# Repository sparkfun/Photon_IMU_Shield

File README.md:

SparkFun Photon IMU Shield
========================================

[*SparkFun Photon IMU Shield (DEV-13629)*](https://www.sparkfun.com/products/13629)

The [SparkFun Photon IMU Shield](https://www.sparkfun.com/products/13629) is a versatile motion-sensing add-on board for your Photon. It features an LSM9DS1 system-in-a-chip that houses a 3-axis accelerometer, 3-axis gyroscope, and 3-axis magnetometer. That’s right, 9 degrees of freedom (9DOF) from a single IC!

Each sensor in the LSM9DS1 supports a large variety of ranges: the accelerometer’s scale can be set to ± 2, 4, 6, 8, or 16 g, the gyroscope supports ± 245, 500, and 2000 °/s, and the magnetometer has full-scale ranges of ± 2, 4, 8, or 12 gauss. The SparkFun Photon IMU Shield comes with the headers already soldered on, so you can plug and play!

Repository Contents
-------------------

* **/Hardware** - Eagle design files (.brd, .sch)
* **/Production** - Production panel files (.brd)
* **/Libraries** - Firmware library and example code for the Particle Photon.

Documentation
--------------
* **[Hookup Guide](https://learn.sparkfun.com/tutorials/photon-imu-shield-hookup-guide)** - Hardware overview and example code.

Product Versions
----------------
* [DEV-13629](https://www.sparkfun.com/products/13629)- V1.0 release of the Photon IMU Shield.

License Information
-------------------
This product is _**open source**_! 

The **hardware** is released under [Creative Commons ShareAlike 4.0 International](https://creativecommons.org/licenses/by-sa/4.0/).

The **code**  license can be found in the source directory.

Please use, reuse, and modify these files as you see fit. Please maintain attribution to SparkFun Electronics and release anything derivative under the same license.

Distributed as-is; no warranty is given.

- Your friends at SparkFun.

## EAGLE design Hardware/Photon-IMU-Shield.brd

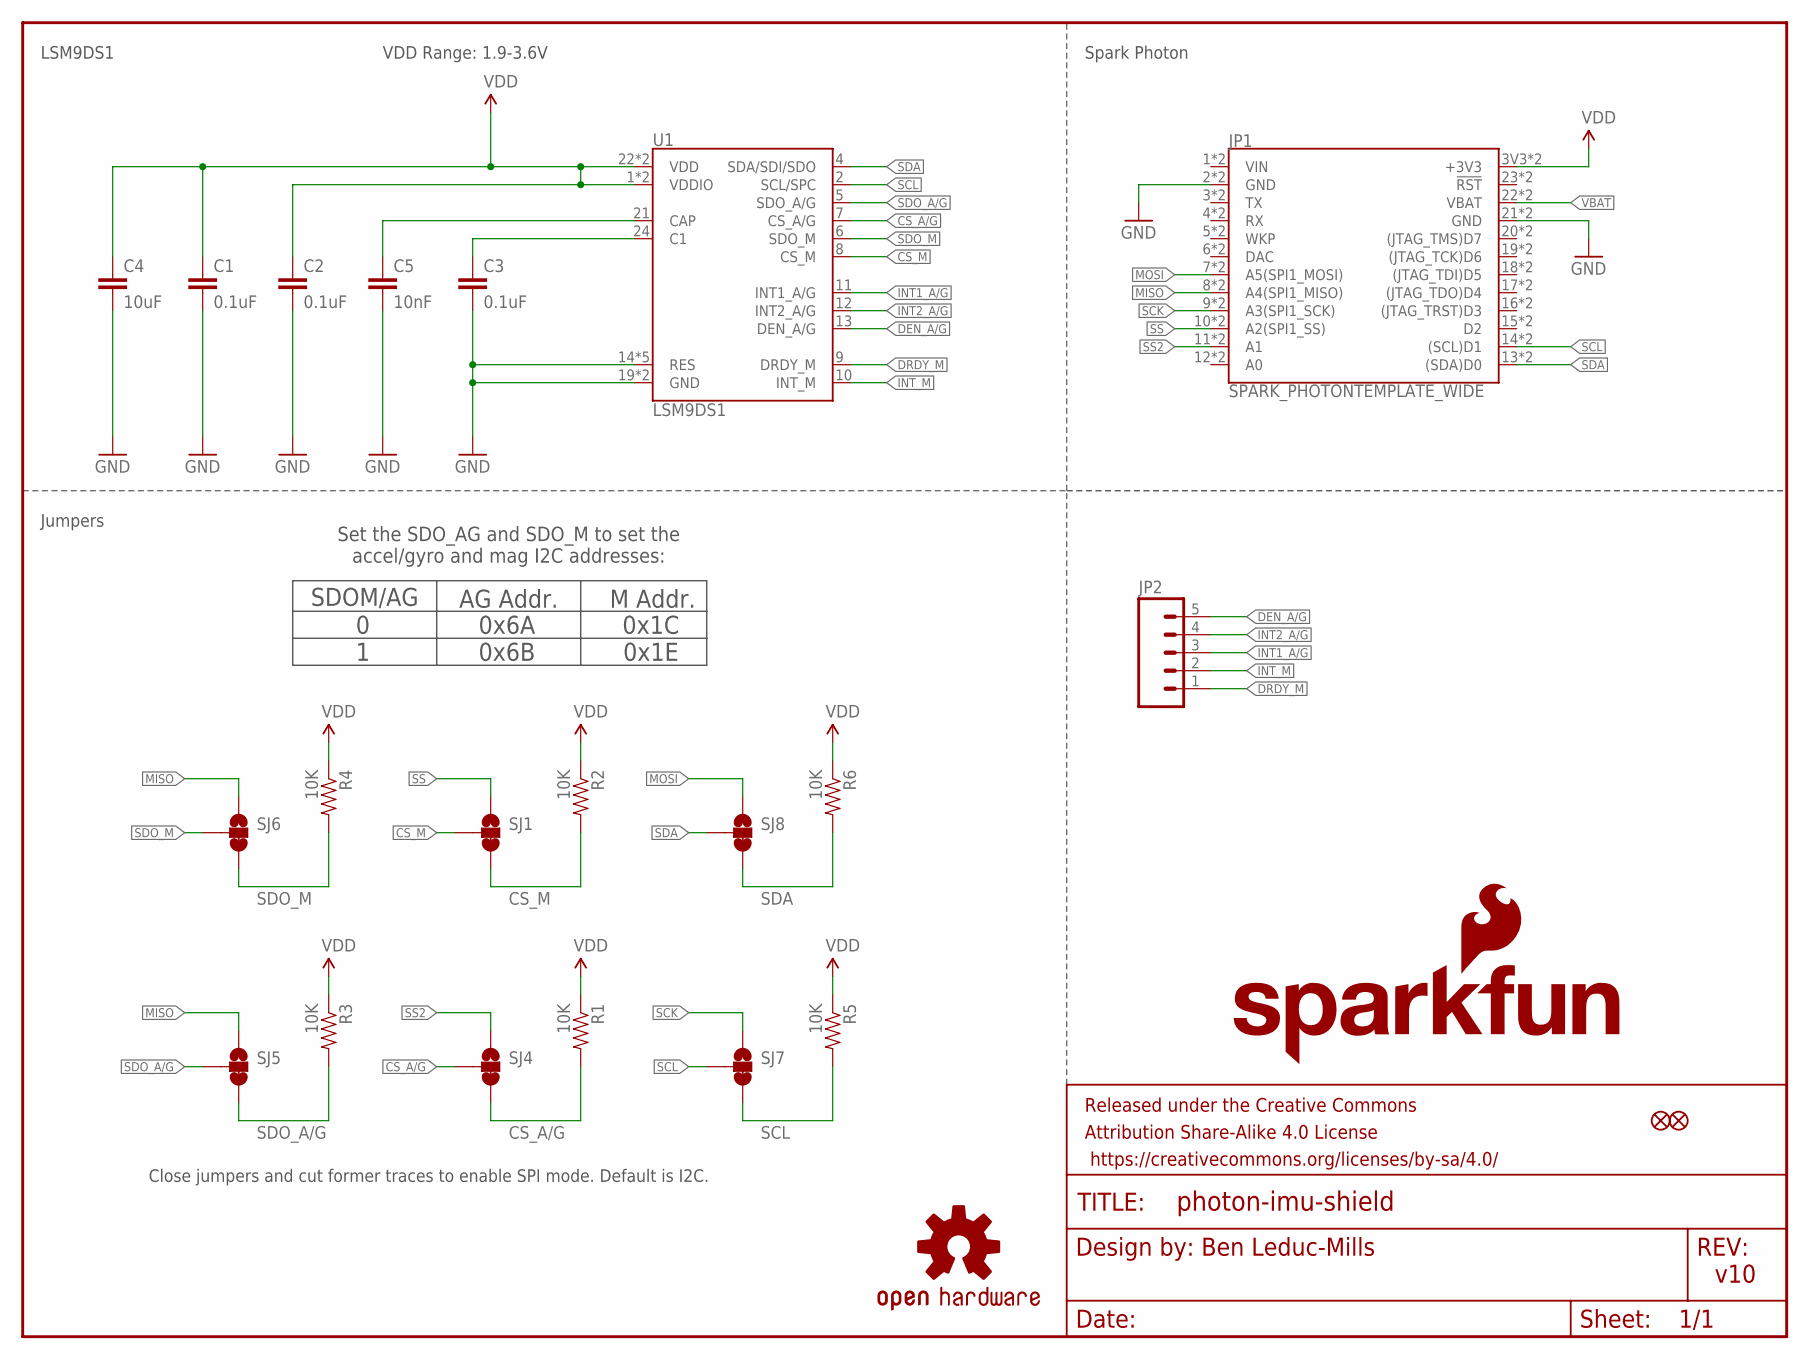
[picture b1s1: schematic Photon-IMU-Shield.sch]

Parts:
C1, C2, C3: 0.1uF; 0603-CAP
C4: 10uF; 0603-CAP
C5: 10nF; 0603-CAP
FID1, FID2: FIDUCIAL1X2; FIDUCIAL-1X2
FRAME1: FRAME-LETTER; CREATIVE_COMMONS
JP1: SPARK_PHOTONTEMPLATE_WIDE; SPARK_PHOTON_TEMPLATE_WIDE
JP2: M05PTH; 1X05
LOGO1: SFE_LOGO_NAME_FLAME.1_INCH; SFE_LOGO_NAME_FLAME_.1
LOGO2: OSHW-LOGOS; OSHW-LOGO-S
R1, R2, R3, R4, R5, R6: 10K; 0603-RES
SJ1, SJ4, SJ5, SJ6, SJ7, SJ8: JUMPER-PAD-3-2OF3_NC_BY_TRACE_SMALL; PAD-JUMPER-3-2OF3_NC_BY_TRACE_YES_SILK_FULL_BOX
U1: LSM9DS1; LGA24-8X4

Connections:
CS_A/G: R1.2, SJ4.2, SJ4.3, U1.7 (CS_A/G)
CS_M: R2.2, SJ1.2, SJ1.3, U1.8 (CS_M)
DEN_A/G: JP2.5, U1.13 (DEN_A/G)
DRDY_M: JP2.1, U1.9 (DRDY_M)
GND: C1.2, C2.2, C3.2, C4.2, C5.2, JP1.2 (GND), JP1.21 (GND), JP1.GND@0 (GND), JP1.GND@2 (GND), U1.14 (RES), U1.15 (RES), U1.16 (RES), U1.17 (RES), U1.18 (RES), U1.19 (GND), U1.20 (GND)
INT1_A/G: JP2.3, U1.11 (INT1_A/G)
INT2_A/G: JP2.4, U1.12 (INT2_A/G)
INT_M: JP2.2, U1.10 (INT_M)
MISO: JP1.8 (A4(SPI1_MISO)), JP1.A4 (A4(SPI1_MISO)), SJ5.1, SJ6.1
MOSI: JP1.7 (A5(SPI1_MOSI)), JP1.A5 (A5(SPI1_MOSI)), SJ8.1
unnamed: C5.1, U1.21 (CAP)
unnamed: C3.1, U1.24 (C1)
SCK: JP1.9 (A3(SPI1_SCK)), JP1.A3 (A3(SPI1_SCK)), SJ7.1
SCL: JP1.14 ((SCL)D1), JP1.D1 ((SCL)D1), R5.2, SJ7.2, SJ7.3, U1.2 (SCL/SPC)
SDA: JP1.13 ((SDA)D0), JP1.D0 ((SDA)D0), R6.2, SJ8.2, SJ8.3, U1.4 (SDA/SDI/SDO)
SDO_A/G: R3.2, SJ5.2, SJ5.3, U1.5 (SDO_A/G)
SDO_M: R4.2, SJ6.2, SJ6.3, U1.6 (SDO_M)
SS: JP1.10 (A2(SPI1_SS)), JP1.A2 (A2(SPI1_SS)), SJ1.1
SS2: JP1.11 (A1), JP1.A1, SJ4.1
VBAT: JP1.22 (VBAT), JP1.VBAT
VDD: C1.1, C2.1, C4.1, JP1.3V3 (+3V3), JP1.24 (+3V3), R1.1, R2.1, R3.1, R4.1, R5.1, R6.1, U1.1 (VDDIO), U1.3 (VDDIO), U1.22 (VDD), U1.23 (VDD)

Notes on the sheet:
Close jumpers and cut former traces to enable SPI mode. Default is I2C.
VDD Range: 1.9-3.6V
LSM9DS1
Spark Photon
Jumpers
SDOM/AG
0x1C 0x1E
AG Addr.
0 1
M Addr.
0x6A 0x6B
Set the SDO_AG and SDO_M to set the accel/gyro and mag I2C addresses:
v10

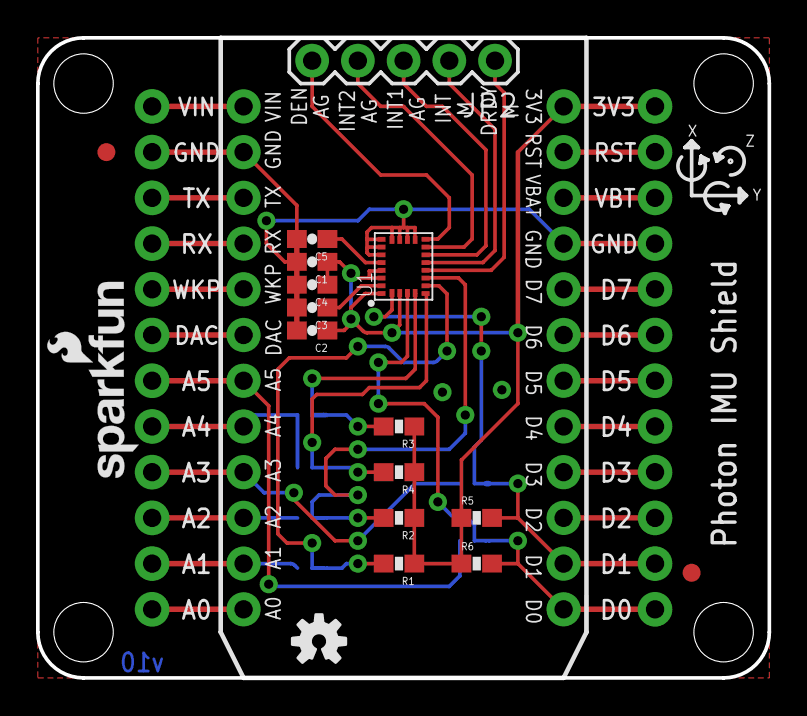
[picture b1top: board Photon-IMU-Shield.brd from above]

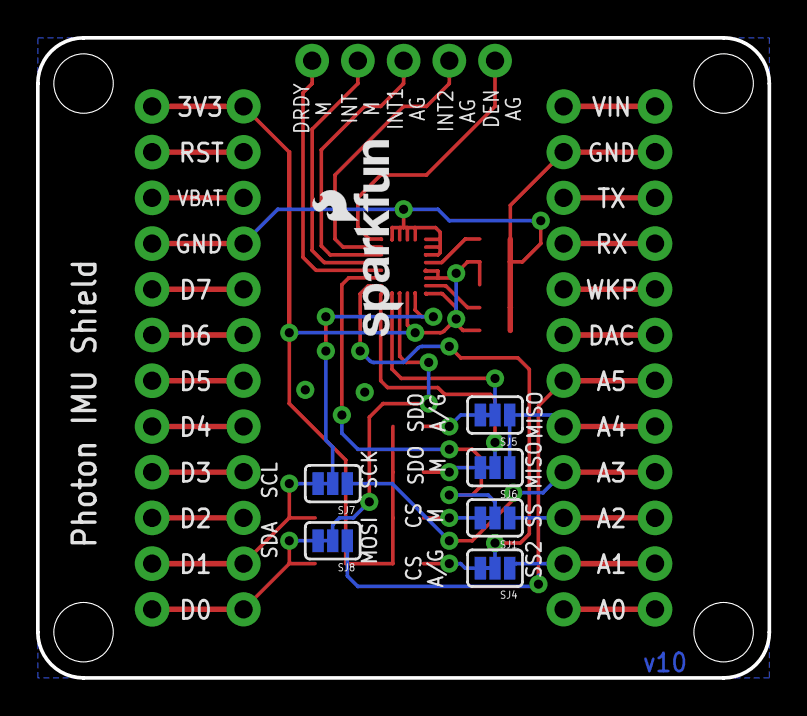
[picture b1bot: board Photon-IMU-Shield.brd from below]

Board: 2 copper layers, 40.6 x 35.6 mm, 26 parts (7 on the bottom side), 21 nets.

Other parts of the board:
U$5: SFE_LOGO_NAME_FLAME_.1

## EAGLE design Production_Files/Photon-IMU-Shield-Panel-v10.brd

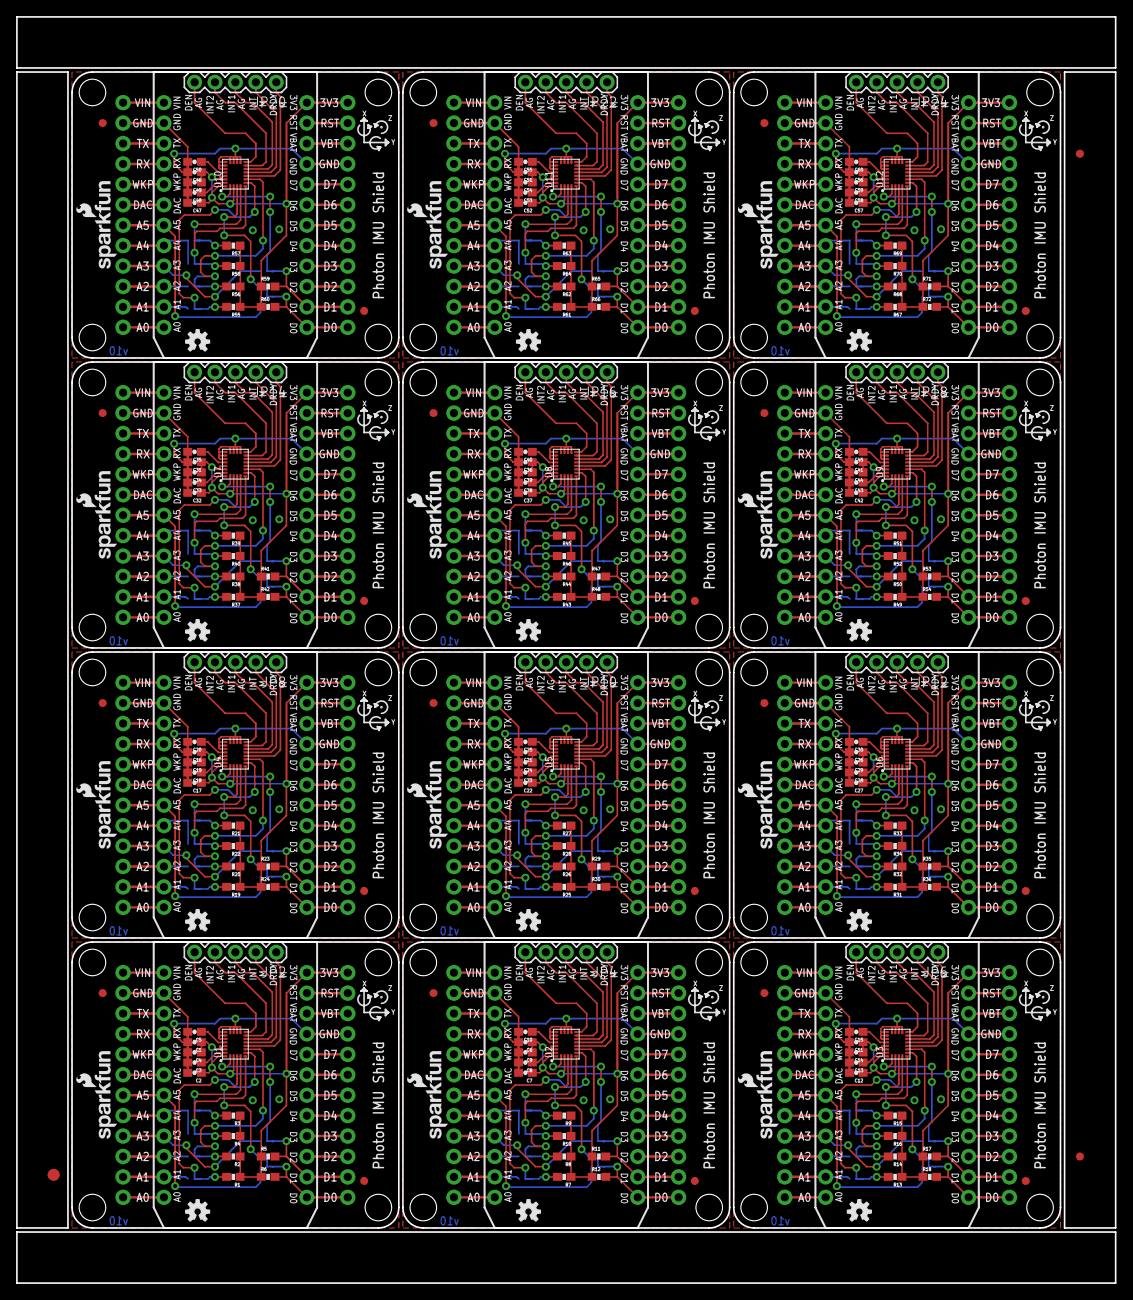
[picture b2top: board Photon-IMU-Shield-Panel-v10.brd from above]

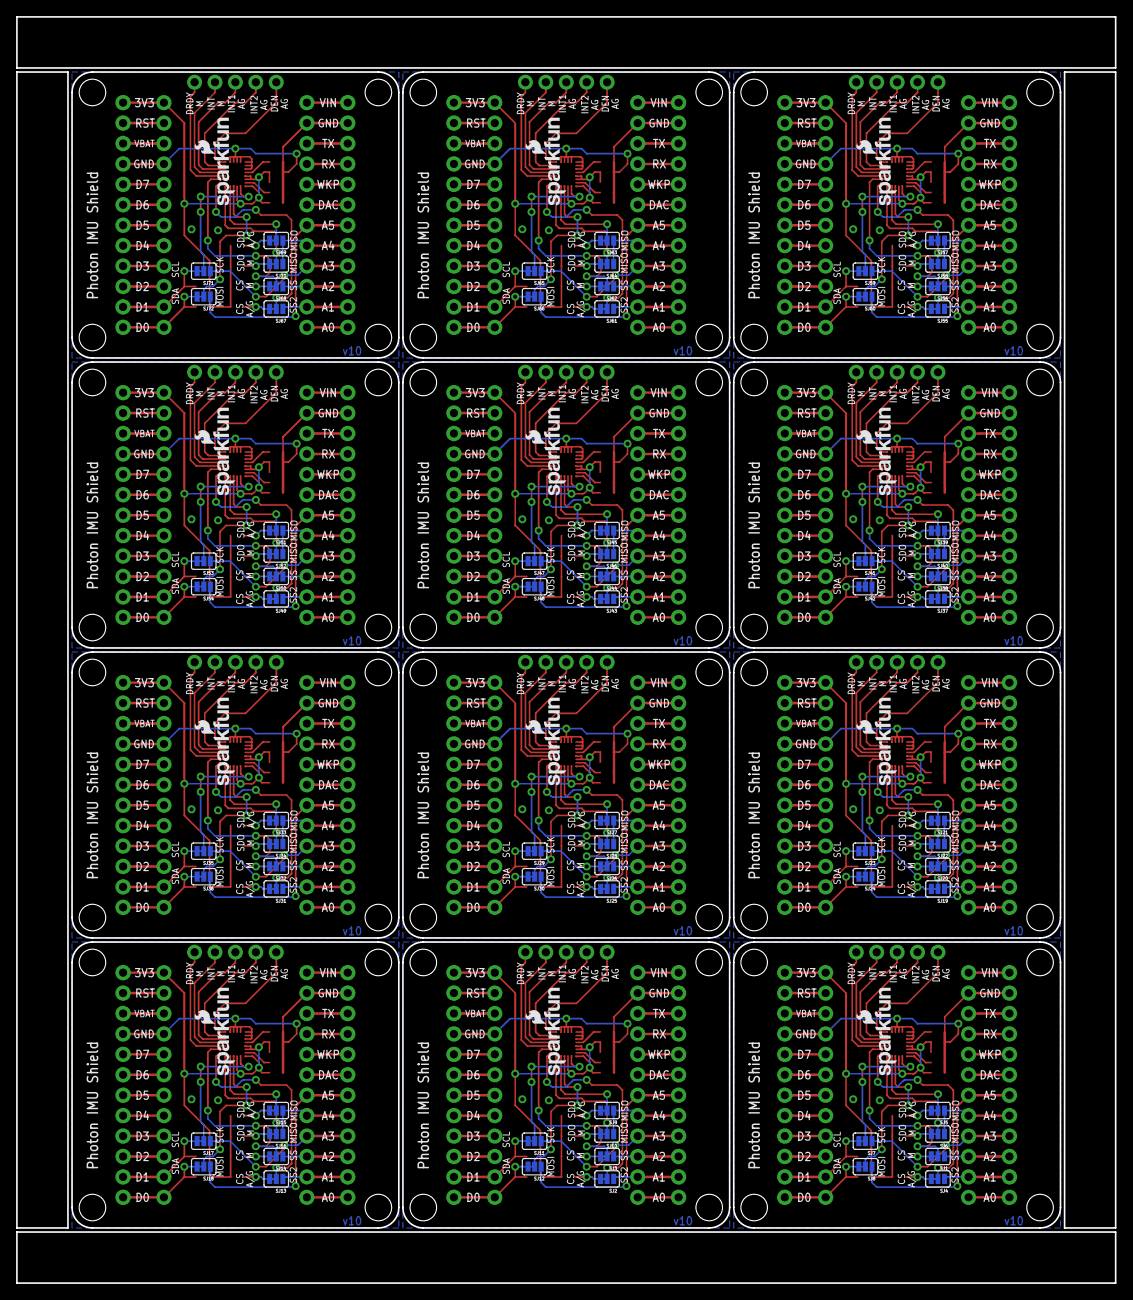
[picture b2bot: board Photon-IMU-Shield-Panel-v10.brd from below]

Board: 2 copper layers, 136.7 x 157.5 mm, 303 parts (84 on the bottom side), 252 nets.

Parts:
C1, C2, C3, C6, C7, C8, C11, C12, C13, C16, C17, C18, C21, C22, C23, C26, C27, C28, C31, C32, C33, C36, C37, C38, C41, C42, C43, C46, C47, C48, C51, C52, C53, C56, C57, C58: 0.1uF; 0603-CAP
C4, C9, C14, C19, C24, C29, C34, C39, C44, C49, C54, C59: 10uF; 0603-CAP
C5, C10, C15, C20, C25, C30, C35, C40, C45, C50, C55, C60: 10nF; 0603-CAP
E$1: FIDUCIAL-1.5X3
E$4, E$5: FIDUCIAL-1X2
FID1, FID2, FID3, FID4, FID5, FID6, FID7, FID8, FID9, FID10, FID11, FID12, FID13, FID14, FID15, FID16, FID17, FID18, FID19, FID20, FID21, FID22, FID23, FID24: FIDUCIAL1X2; FIDUCIAL-1X2
JP1, JP3, JP5, JP7, JP9, JP11, JP13, JP15, JP17, JP19, JP21, JP23: SPARK_PHOTONTEMPLATE_WIDE; SPARK_PHOTON_TEMPLATE_WIDE
JP2, JP4, JP6, JP8, JP10, JP12, JP14, JP16, JP18, JP20, JP22, JP24: 1X05
LOGO1, LOGO4, LOGO6, LOGO8, LOGO10, LOGO12, LOGO14, LOGO16, LOGO18, LOGO20, LOGO22, LOGO24: SFE_LOGO_NAME_FLAME.1_INCH; SFE_LOGO_NAME_FLAME_.1
LOGO2, LOGO3, LOGO5, LOGO7, LOGO9, LOGO11, LOGO13, LOGO15, LOGO17, LOGO19, LOGO21, LOGO23: OSHW-LOGOS; OSHW-LOGO-S
R1, R2, R3, R4, R5, R6, R7, R8, R9, R10, R11, R12, R13, R14, R15, R16, R17, R18, R19, R20, R21, R22, R23, R24, R25, R26, R27, R28, R29, R30, R31, R32, R33, R34, R35, R36, R37, R38, R39, R40, R41, R42, R43, R44, R45, R46, R47, R48, R49, R50, R51, R52, R53, R54, R55, R56, R57, R58, R59, R60, R61, R62, R63, R64, R65, R66, R67, R68, R69, R70, R71, R72: 10K; 0603-RES
SJ1, SJ2, SJ3, SJ4, SJ5, SJ6, SJ7, SJ8, SJ9, SJ10, SJ11, SJ12, SJ13, SJ14, SJ15, SJ16, SJ17, SJ18, SJ19, SJ20, SJ21, SJ22, SJ23, SJ24, SJ25, SJ26, SJ27, SJ28, SJ29, SJ30, SJ31, SJ32, SJ33, SJ34, SJ35, SJ36, SJ37, SJ38, SJ39, SJ40, SJ41, SJ42, SJ43, SJ44, SJ45, SJ46, SJ47, SJ48, SJ49, SJ50, SJ51, SJ52, SJ53, SJ54, SJ55, SJ56, SJ57, SJ58, SJ59, SJ60, SJ61, SJ62, SJ63, SJ64, SJ65, SJ66, SJ67, SJ68, SJ69, SJ70, SJ71, SJ72: PAD-JUMPER-3-2OF3_NC_BY_TRACE_YES_SILK_FULL_BOX
U1, U2, U3, U4, U5, U6, U7, U8, U9, U10, U11, U12: LSM9DS1; LGA24-8X4
U$1, U$2, U$3, U$4, U$5, U$6, U$7, U$8, U$9, U$10, U$11, U$12: SFE_LOGO_NAME_FLAME_.1

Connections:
CS_A/G: R1.2, SJ4.2, SJ4.3, U1.7
CS_A/G1: R7.2, SJ2.2, SJ2.3, U2.7
CS_A/G2: R13.2, SJ13.2, SJ13.3, U3.7
CS_A/G3: R19.2, SJ19.2, SJ19.3, U4.7
CS_A/G4: R25.2, SJ25.2, SJ25.3, U5.7
CS_A/G5: R31.2, SJ31.2, SJ31.3, U6.7
CS_A/G6: R37.2, SJ37.2, SJ37.3, U7.7
CS_A/G7: R43.2, SJ43.2, SJ43.3, U8.7
CS_A/G8: R49.2, SJ49.2, SJ49.3, U9.7
CS_A/G9: R55.2, SJ55.2, SJ55.3, U10.7
CS_A/G10: R61.2, SJ61.2, SJ61.3, U11.7
CS_A/G11: R67.2, SJ67.2, SJ67.3, U12.7
CS_M: R2.2, SJ1.2, SJ1.3, U1.8
CS_M1: R8.2, SJ3.2, SJ3.3, U2.8
CS_M2: R14.2, SJ14.2, SJ14.3, U3.8
CS_M3: R20.2, SJ20.2, SJ20.3, U4.8
CS_M4: R26.2, SJ26.2, SJ26.3, U5.8
CS_M5: R32.2, SJ32.2, SJ32.3, U6.8
CS_M6: R38.2, SJ38.2, SJ38.3, U7.8
CS_M7: R44.2, SJ44.2, SJ44.3, U8.8
CS_M8: R50.2, SJ50.2, SJ50.3, U9.8
CS_M9: R56.2, SJ56.2, SJ56.3, U10.8
CS_M10: R62.2, SJ62.2, SJ62.3, U11.8
CS_M11: R68.2, SJ68.2, SJ68.3, U12.8
DEN_A/G: JP2.5, U1.13
DEN_A/G1: JP4.5, U2.13
DEN_A/G2: JP6.5, U3.13
DEN_A/G3: JP8.5, U4.13
DEN_A/G4: JP10.5, U5.13
DEN_A/G5: JP12.5, U6.13
DEN_A/G6: JP14.5, U7.13
DEN_A/G7: JP16.5, U8.13
DEN_A/G8: JP18.5, U9.13
DEN_A/G9: JP20.5, U10.13
DEN_A/G10: JP22.5, U11.13
DEN_A/G11: JP24.5, U12.13
DRDY_M: JP2.1, U1.9
DRDY_M1: JP4.1, U2.9
DRDY_M2: JP6.1, U3.9
DRDY_M3: JP8.1, U4.9
DRDY_M4: JP10.1, U5.9
DRDY_M5: JP12.1, U6.9
DRDY_M6: JP14.1, U7.9
DRDY_M7: JP16.1, U8.9
DRDY_M8: JP18.1, U9.9
DRDY_M9: JP20.1, U10.9
DRDY_M10: JP22.1, U11.9
DRDY_M11: JP24.1, U12.9
GND: C1.2, C2.2, C3.2, C4.2, C5.2, JP1.2, JP1.21, JP1.GND@0, JP1.GND@2, U1.14, U1.15, U1.16, U1.17, U1.18, U1.19, U1.20
GND1: C6.2, C7.2, C8.2, C9.2, C10.2, JP3.2, JP3.21, JP3.GND@0, JP3.GND@2, U2.14, U2.15, U2.16, U2.17, U2.18, U2.19, U2.20
GND2: C11.2, C12.2, C13.2, C14.2, C15.2, JP5.2, JP5.21, JP5.GND@0, JP5.GND@2, U3.14, U3.15, U3.16, U3.17, U3.18, U3.19, U3.20
GND3: C16.2, C17.2, C18.2, C19.2, C20.2, JP7.2, JP7.21, JP7.GND@0, JP7.GND@2, U4.14, U4.15, U4.16, U4.17, U4.18, U4.19, U4.20
GND4: C21.2, C22.2, C23.2, C24.2, C25.2, JP9.2, JP9.21, JP9.GND@0, JP9.GND@2, U5.14, U5.15, U5.16, U5.17, U5.18, U5.19, U5.20
GND5: C26.2, C27.2, C28.2, C29.2, C30.2, JP11.2, JP11.21, JP11.GND@0, JP11.GND@2, U6.14, U6.15, U6.16, U6.17, U6.18, U6.19, U6.20
GND6: C31.2, C32.2, C33.2, C34.2, C35.2, JP13.2, JP13.21, JP13.GND@0, JP13.GND@2, U7.14, U7.15, U7.16, U7.17, U7.18, U7.19, U7.20
GND7: C36.2, C37.2, C38.2, C39.2, C40.2, JP15.2, JP15.21, JP15.GND@0, JP15.GND@2, U8.14, U8.15, U8.16, U8.17, U8.18, U8.19, U8.20
GND8: C41.2, C42.2, C43.2, C44.2, C45.2, JP17.2, JP17.21, JP17.GND@0, JP17.GND@2, U9.14, U9.15, U9.16, U9.17, U9.18, U9.19, U9.20
GND9: C46.2, C47.2, C48.2, C49.2, C50.2, JP19.2, JP19.21, JP19.GND@0, JP19.GND@2, U10.14, U10.15, U10.16, U10.17, U10.18, U10.19, U10.20
GND10: C51.2, C52.2, C53.2, C54.2, C55.2, JP21.2, JP21.21, JP21.GND@0, JP21.GND@2, U11.14, U11.15, U11.16, U11.17, U11.18, U11.19, U11.20
GND11: C56.2, C57.2, C58.2, C59.2, C60.2, JP23.2, JP23.21, JP23.GND@0, JP23.GND@2, U12.14, U12.15, U12.16, U12.17, U12.18, U12.19, U12.20
INT1_A/G: JP2.3, U1.11
INT1_A/G1: JP4.3, U2.11
INT1_A/G2: JP6.3, U3.11
INT1_A/G3: JP8.3, U4.11
INT1_A/G4: JP10.3, U5.11
INT1_A/G5: JP12.3, U6.11
INT1_A/G6: JP14.3, U7.11
INT1_A/G7: JP16.3, U8.11
INT1_A/G8: JP18.3, U9.11
INT1_A/G9: JP20.3, U10.11
INT1_A/G10: JP22.3, U11.11
INT1_A/G11: JP24.3, U12.11
INT2_A/G: JP2.4, U1.12
INT2_A/G1: JP4.4, U2.12
INT2_A/G2: JP6.4, U3.12
INT2_A/G3: JP8.4, U4.12
INT2_A/G4: JP10.4, U5.12
INT2_A/G5: JP12.4, U6.12
INT2_A/G6: JP14.4, U7.12
INT2_A/G7: JP16.4, U8.12
INT2_A/G8: JP18.4, U9.12
INT2_A/G9: JP20.4, U10.12
INT2_A/G10: JP22.4, U11.12
INT2_A/G11: JP24.4, U12.12
INT_M: JP2.2, U1.10
INT_M1: JP4.2, U2.10
INT_M2: JP6.2, U3.10
INT_M3: JP8.2, U4.10
INT_M4: JP10.2, U5.10
INT_M5: JP12.2, U6.10
INT_M6: JP14.2, U7.10
INT_M7: JP16.2, U8.10
INT_M8: JP18.2, U9.10
INT_M9: JP20.2, U10.10
INT_M10: JP22.2, U11.10
INT_M11: JP24.2, U12.10
MISO: JP1.8, JP1.A4, SJ5.1, SJ6.1
MISO1: JP3.8, JP3.A4, SJ9.1, SJ10.1
MISO2: JP5.8, JP5.A4, SJ15.1, SJ16.1
MISO3: JP7.8, JP7.A4, SJ21.1, SJ22.1
MISO4: JP9.8, JP9.A4, SJ27.1, SJ28.1
MISO5: JP11.8, JP11.A4, SJ33.1, SJ34.1
MISO6: JP13.8, JP13.A4, SJ39.1, SJ40.1
MISO7: JP15.8, JP15.A4, SJ45.1, SJ46.1
MISO8: JP17.8, JP17.A4, SJ51.1, SJ52.1
MISO9: JP19.8, JP19.A4, SJ57.1, SJ58.1
MISO10: JP21.8, JP21.A4, SJ63.1, SJ64.1
MISO11: JP23.8, JP23.A4, SJ69.1, SJ70.1
MOSI: JP1.7, JP1.A5, SJ8.1
MOSI1: JP3.7, JP3.A5, SJ12.1
MOSI2: JP5.7, JP5.A5, SJ18.1
MOSI3: JP7.7, JP7.A5, SJ24.1
MOSI4: JP9.7, JP9.A5, SJ30.1
MOSI5: JP11.7, JP11.A5, SJ36.1
MOSI6: JP13.7, JP13.A5, SJ42.1
MOSI7: JP15.7, JP15.A5, SJ48.1
MOSI8: JP17.7, JP17.A5, SJ54.1
MOSI9: JP19.7, JP19.A5, SJ60.1
MOSI10: JP21.7, JP21.A5, SJ66.1
MOSI11: JP23.7, JP23.A5, SJ72.1
unnamed: C10.1, U2.21
unnamed: C8.1, U2.24
unnamed: C5.1, U1.21
unnamed: C3.1, U1.24
unnamed: C15.1, U3.21
unnamed: C13.1, U3.24
unnamed: C20.1, U4.21
unnamed: C18.1, U4.24
unnamed: C25.1, U5.21
unnamed: C23.1, U5.24
unnamed: C30.1, U6.21
unnamed: C28.1, U6.24
unnamed: C35.1, U7.21
unnamed: C33.1, U7.24
unnamed: C40.1, U8.21
unnamed: C38.1, U8.24
unnamed: C45.1, U9.21
unnamed: C43.1, U9.24
unnamed: C50.1, U10.21
unnamed: C48.1, U10.24
unnamed: C55.1, U11.21
unnamed: C53.1, U11.24
unnamed: C60.1, U12.21
unnamed: C58.1, U12.24
SCK: JP1.9, JP1.A3, SJ7.1
SCK1: JP3.9, JP3.A3, SJ11.1
SCK2: JP5.9, JP5.A3, SJ17.1
SCK3: JP7.9, JP7.A3, SJ23.1
SCK4: JP9.9, JP9.A3, SJ29.1
SCK5: JP11.9, JP11.A3, SJ35.1
SCK6: JP13.9, JP13.A3, SJ41.1
SCK7: JP15.9, JP15.A3, SJ47.1
SCK8: JP17.9, JP17.A3, SJ53.1
SCK9: JP19.9, JP19.A3, SJ59.1
SCK10: JP21.9, JP21.A3, SJ65.1
SCK11: JP23.9, JP23.A3, SJ71.1
SCL: JP1.14, JP1.D1, R5.2, SJ7.2, SJ7.3, U1.2
SCL1: JP3.14, JP3.D1, R11.2, SJ11.2, SJ11.3, U2.2
SCL2: JP5.14, JP5.D1, R17.2, SJ17.2, SJ17.3, U3.2
SCL3: JP7.14, JP7.D1, R23.2, SJ23.2, SJ23.3, U4.2
SCL4: JP9.14, JP9.D1, R29.2, SJ29.2, SJ29.3, U5.2
SCL5: JP11.14, JP11.D1, R35.2, SJ35.2, SJ35.3, U6.2
SCL6: JP13.14, JP13.D1, R41.2, SJ41.2, SJ41.3, U7.2
SCL7: JP15.14, JP15.D1, R47.2, SJ47.2, SJ47.3, U8.2
SCL8: JP17.14, JP17.D1, R53.2, SJ53.2, SJ53.3, U9.2
SCL9: JP19.14, JP19.D1, R59.2, SJ59.2, SJ59.3, U10.2
SCL10: JP21.14, JP21.D1, R65.2, SJ65.2, SJ65.3, U11.2
SCL11: JP23.14, JP23.D1, R71.2, SJ71.2, SJ71.3, U12.2
SDA: JP1.13, JP1.D0, R6.2, SJ8.2, SJ8.3, U1.4
SDA1: JP3.13, JP3.D0, R12.2, SJ12.2, SJ12.3, U2.4
SDA2: JP5.13, JP5.D0, R18.2, SJ18.2, SJ18.3, U3.4
SDA3: JP7.13, JP7.D0, R24.2, SJ24.2, SJ24.3, U4.4
SDA4: JP9.13, JP9.D0, R30.2, SJ30.2, SJ30.3, U5.4
SDA5: JP11.13, JP11.D0, R36.2, SJ36.2, SJ36.3, U6.4
SDA6: JP13.13, JP13.D0, R42.2, SJ42.2, SJ42.3, U7.4
SDA7: JP15.13, JP15.D0, R48.2, SJ48.2, SJ48.3, U8.4
SDA8: JP17.13, JP17.D0, R54.2, SJ54.2, SJ54.3, U9.4
SDA9: JP19.13, JP19.D0, R60.2, SJ60.2, SJ60.3, U10.4
SDA10: JP21.13, JP21.D0, R66.2, SJ66.2, SJ66.3, U11.4
SDA11: JP23.13, JP23.D0, R72.2, SJ72.2, SJ72.3, U12.4
SDO_A/G: R3.2, SJ5.2, SJ5.3, U1.5
SDO_A/G1: R9.2, SJ9.2, SJ9.3, U2.5
SDO_A/G2: R15.2, SJ15.2, SJ15.3, U3.5
SDO_A/G3: R21.2, SJ21.2, SJ21.3, U4.5
SDO_A/G4: R27.2, SJ27.2, SJ27.3, U5.5
SDO_A/G5: R33.2, SJ33.2, SJ33.3, U6.5
SDO_A/G6: R39.2, SJ39.2, SJ39.3, U7.5
SDO_A/G7: R45.2, SJ45.2, SJ45.3, U8.5
SDO_A/G8: R51.2, SJ51.2, SJ51.3, U9.5
SDO_A/G9: R57.2, SJ57.2, SJ57.3, U10.5
SDO_A/G10: R63.2, SJ63.2, SJ63.3, U11.5
SDO_A/G11: R69.2, SJ69.2, SJ69.3, U12.5
SDO_M: R4.2, SJ6.2, SJ6.3, U1.6
SDO_M1: R10.2, SJ10.2, SJ10.3, U2.6
SDO_M2: R16.2, SJ16.2, SJ16.3, U3.6
SDO_M3: R22.2, SJ22.2, SJ22.3, U4.6
SDO_M4: R28.2, SJ28.2, SJ28.3, U5.6
SDO_M5: R34.2, SJ34.2, SJ34.3, U6.6
SDO_M6: R40.2, SJ40.2, SJ40.3, U7.6
SDO_M7: R46.2, SJ46.2, SJ46.3, U8.6
SDO_M8: R52.2, SJ52.2, SJ52.3, U9.6
SDO_M9: R58.2, SJ58.2, SJ58.3, U10.6
SDO_M10: R64.2, SJ64.2, SJ64.3, U11.6
SDO_M11: R70.2, SJ70.2, SJ70.3, U12.6
SS: JP1.10, JP1.A2, SJ1.1
SS1: JP3.10, JP3.A2, SJ3.1
SS2: JP1.11, JP1.A1, SJ4.1
SS3: JP3.11, JP3.A1, SJ2.1
SS4: JP5.10, JP5.A2, SJ14.1
SS5: JP5.11, JP5.A1, SJ13.1
SS6: JP7.10, JP7.A2, SJ20.1
SS7: JP7.11, JP7.A1, SJ19.1
SS8: JP9.10, JP9.A2, SJ26.1
SS9: JP9.11, JP9.A1, SJ25.1
SS10: JP11.10, JP11.A2, SJ32.1
SS11: JP11.11, JP11.A1, SJ31.1
SS12: JP13.10, JP13.A2, SJ38.1
SS13: JP13.11, JP13.A1, SJ37.1
SS14: JP15.10, JP15.A2, SJ44.1
SS15: JP15.11, JP15.A1, SJ43.1
SS16: JP17.10, JP17.A2, SJ50.1
SS17: JP17.11, JP17.A1, SJ49.1
SS18: JP19.10, JP19.A2, SJ56.1
SS19: JP19.11, JP19.A1, SJ55.1
SS20: JP21.10, JP21.A2, SJ62.1
SS21: JP21.11, JP21.A1, SJ61.1
SS22: JP23.10, JP23.A2, SJ68.1
SS23: JP23.11, JP23.A1, SJ67.1
VBAT: JP1.22, JP1.VBAT
VBAT1: JP3.22, JP3.VBAT
VBAT2: JP5.22, JP5.VBAT
VBAT3: JP7.22, JP7.VBAT
VBAT4: JP9.22, JP9.VBAT
VBAT5: JP11.22, JP11.VBAT
VBAT6: JP13.22, JP13.VBAT
VBAT7: JP15.22, JP15.VBAT
VBAT8: JP17.22, JP17.VBAT
VBAT9: JP19.22, JP19.VBAT
VBAT10: JP21.22, JP21.VBAT
VBAT11: JP23.22, JP23.VBAT
VDD: C1.1, C2.1, C4.1, JP1.3V3, JP1.24, R1.1, R2.1, R3.1, R4.1, R5.1, R6.1, U1.1, U1.3, U1.22, U1.23
VDD1: C6.1, C7.1, C9.1, JP3.3V3, JP3.24, R7.1, R8.1, R9.1, R10.1, R11.1, R12.1, U2.1, U2.3, U2.22, U2.23
VDD2: C11.1, C12.1, C14.1, JP5.3V3, JP5.24, R13.1, R14.1, R15.1, R16.1, R17.1, R18.1, U3.1, U3.3, U3.22, U3.23
VDD3: C16.1, C17.1, C19.1, JP7.3V3, JP7.24, R19.1, R20.1, R21.1, R22.1, R23.1, R24.1, U4.1, U4.3, U4.22, U4.23
VDD4: C21.1, C22.1, C24.1, JP9.3V3, JP9.24, R25.1, R26.1, R27.1, R28.1, R29.1, R30.1, U5.1, U5.3, U5.22, U5.23
VDD5: C26.1, C27.1, C29.1, JP11.3V3, JP11.24, R31.1, R32.1, R33.1, R34.1, R35.1, R36.1, U6.1, U6.3, U6.22, U6.23
VDD6: C31.1, C32.1, C34.1, JP13.3V3, JP13.24, R37.1, R38.1, R39.1, R40.1, R41.1, R42.1, U7.1, U7.3, U7.22, U7.23
VDD7: C36.1, C37.1, C39.1, JP15.3V3, JP15.24, R43.1, R44.1, R45.1, R46.1, R47.1, R48.1, U8.1, U8.3, U8.22, U8.23
VDD8: C41.1, C42.1, C44.1, JP17.3V3, JP17.24, R49.1, R50.1, R51.1, R52.1, R53.1, R54.1, U9.1, U9.3, U9.22, U9.23
VDD9: C46.1, C47.1, C49.1, JP19.3V3, JP19.24, R55.1, R56.1, R57.1, R58.1, R59.1, R60.1, U10.1, U10.3, U10.22, U10.23
VDD10: C51.1, C52.1, C54.1, JP21.3V3, JP21.24, R61.1, R62.1, R63.1, R64.1, R65.1, R66.1, U11.1, U11.3, U11.22, U11.23
VDD11: C56.1, C57.1, C59.1, JP23.3V3, JP23.24, R67.1, R68.1, R69.1, R70.1, R71.1, R72.1, U12.1, U12.3, U12.22, U12.23

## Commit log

2015-02-27 First commit
    .brd and .sch upload
2015-02-27 Improved trace spacing
2015-03-02 Fixed silk, added switch vias
    Not adding JST, b/c pins are adjacent so can just solder to them.
2015-03-03 QC fixes
2015-03-03 fixed measures layer
2015-04-01 update
    changed name on silk
2015-05-11 Adding gap between Photon and pin breakouts.
2015-05-11 Reorganizing file structure to match standard.
2015-05-11 Ch-ch-ch-changes
    Moved xyz silk to the side, changed name
2015-05-22 Revising silkscreen name to Photon IMU Shield
2015-05-22 Small silkscreen changes.
2015-05-26 Changed version number font to vector
2015-05-29 created panel v10
2015-07-02 Squashed 'Libraries/Particle/' content from commit ecfc112
    git-subtree-dir: Libraries/Particle
    git-subtree-split: ecfc112d754a973d1518fb4fa33e839a53bcadf1
2015-07-02 Adding README to Libraries directory.
2015-07-02 Standardizing README

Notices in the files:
parts and their libraries:
SparkFun-Capacitors: Licensing: Creative Commons ShareAlike 4.0 International - https://creativecommons.org/licenses/by-sa/4.0
SparkFun-Aesthetics: Released under the Creative Commons Attribution Share-Alike 4.0 License
SparkFun-Aesthetics: Released under the Creative Commons
